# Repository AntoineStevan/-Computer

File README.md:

# The mother board of the µ-C1 project.
This repo and project contain all the files used to create the mother board for the µ-C1 computer project.

## Table Of Content.
 - [0  ](https://github.com/AntoineStevan/uComputer-mother-board/tree/main/#0-prerequisites-toc)  Prerequisites.
 - [1  ](https://github.com/AntoineStevan/uComputer-mother-board/tree/main/#1-some-images-toc)    Some images.
 - [2  ](https://github.com/AntoineStevan/uComputer-mother-board/tree/main/#2-open-in-kicad-toc)  Open in KiCAD.
 - [2.1](https://github.com/AntoineStevan/uComputer-mother-board/tree/main/#21-install-kicad-toc) Install KiCAD.
 - [2.2](https://github.com/AntoineStevan/uComputer-mother-board/tree/main/#22-use-kicad-toc)     Use KiCAD.

## 0. Prerequisites. [[toc](https://github.com/AntoineStevan/uComputer-mother-board/tree/main/#table-of-content)]
Some schematics and footprints are custom.  
One can find them [here](https://github.com/AntoineStevan/kicad-libraries).

## 1 Some images. [[toc](https://github.com/AntoineStevan/uComputer-mother-board/tree/main/#table-of-content)]
||
|:--:|
| *preview of the schematics.* |

||
|:--:|
| *preview of the pcb design (front side).* |

||
|:--:|
| *preview of the pcb design (back side).* |

## 2. Open in KiCAD. [[toc](https://github.com/AntoineStevan/uComputer-mother-board/tree/main/#table-of-content)]
This project has been designed under KiCAD, which is, according to their official website, *an open-source software tool for the creation of electronic schematic diagrams and PCB artwork.*  
All usefull official documentation can be found on the website of the Kicad software [here](https://www.kicad.org/).  
Furthermore, parts have been ordered by [Mouser](https://www.mouser.fr/) and PCBs have been manufactured by [JLCPCB](https://jlcpcb.com/).

### 2.1. Install KiCAD. [[toc](https://github.com/AntoineStevan/uComputer-mother-board/tree/main/#table-of-content)]
Official KiCAD material can be found [here](https://docs.kicad.org/5.1/en/getting_started_in_kicad/getting_started_in_kicad.html).  
Further specific material for Linux users can be found [here](https://doc.ubuntu-fr.org/kicad).

### 2.2. Use KiCAD. [[toc](https://github.com/AntoineStevan/uComputer-mother-board/tree/main/#table-of-content)]
The KiCAD team provides plenty of documentation and examples on their official website [here](https://docs.kicad.org/).  
The Internet is also full of great quality tutorials on many topics concerning KiCAD software and schematics/PCB design in general.

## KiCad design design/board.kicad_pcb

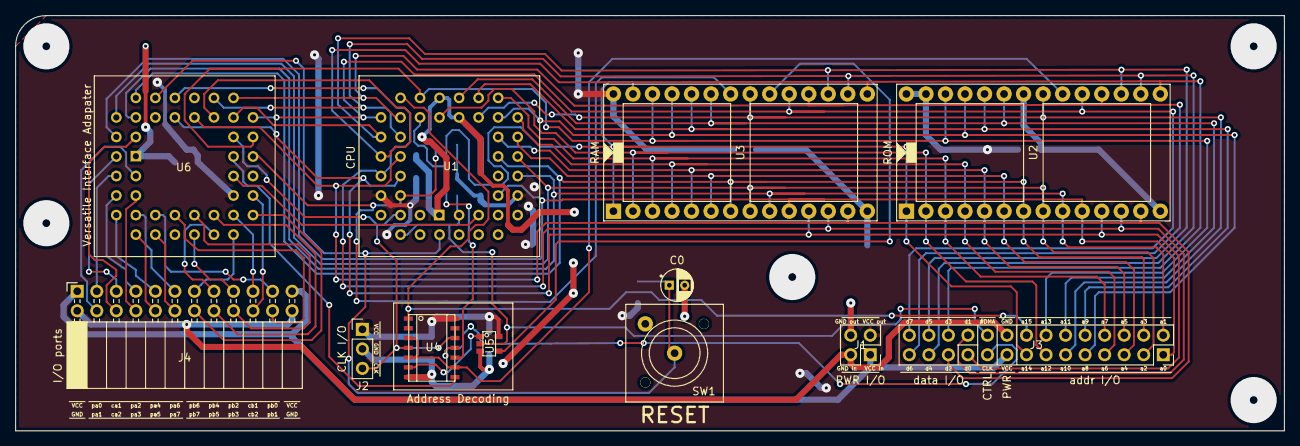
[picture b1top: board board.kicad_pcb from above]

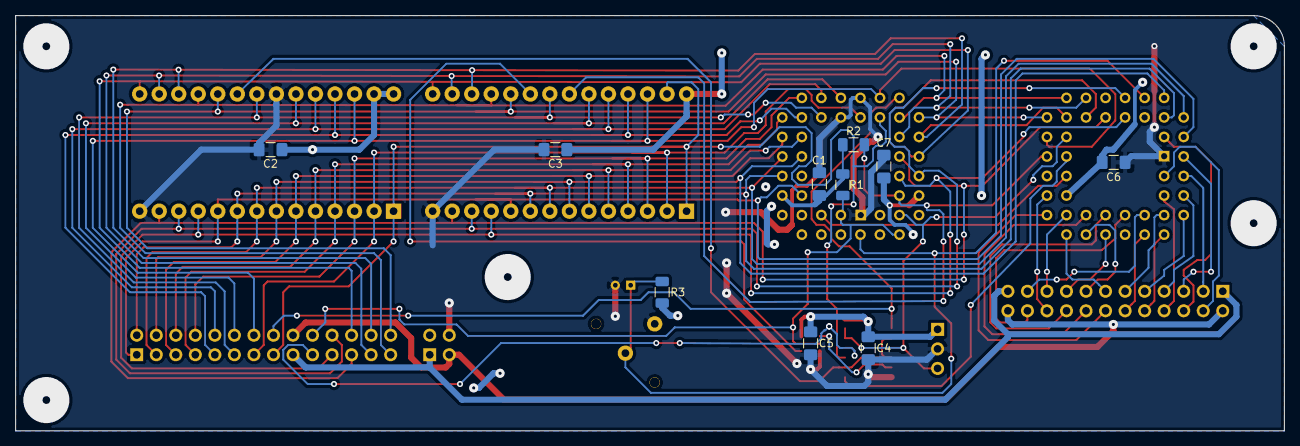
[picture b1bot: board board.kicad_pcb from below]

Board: 2 copper layers, 165.0 x 54.0 mm, 22 parts (10 on the bottom side), 58 nets.

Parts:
C0: C; CP_Radial_D4.0mm_P2.00mm
C1, C2, C3, C4, C5, C6, C7: C; C_1206_3216Metric_Pad1.42x1.75mm_HandSolder
J1: Conn_01x04_Male; PinHeader_2x02_P2.54mm_Vertical
J2: Conn_01x03_Male; PinHeader_1x03_P2.54mm_Vertical
J3: Conn_02x14_Odd_Even; PinSocket_2x14_P2.54mm_Vertical
J4: Conn_02x12_Odd_Even; PinSocket_2x12_P2.54mm_Horizontal
R1, R2, R3: 1K; R_1206_3216Metric
SW1: reset; pushbutton_switch
U1: W65C02_PLCC_44; SOCKET_PLCC_DIP44_A23.5mm_B23.5mm_C12.7mm_D12.7mm_P2.54mm
U2: AT28C256_PDIP_28; DIP_Socket-28_L35.56_W17.78_H5.1_P2.54
U3: SRAM; DIP_Socket-28_L35.56_W17.78_H5.1_P2.54
U4: 74LS00; SOIC_14_L.1.18_W0.58_P1.27
U5: 2-AND; SC-74A_p0.95
U6: W65C22_PLCC_44; SOCKET_PLCC_DIP44_A23.5mm_B23.5mm_C12.7mm_D12.7mm_P2.54mm

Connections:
/#CE: U2.20, U4.3, U4.5, U4.9
/#CLK: J3.19, U4.11
/#CS2: U4.8, U6.25
/#DMA: J3.20, R1.1, U1.3, U1.40, U5.2
/#IRQ: U1.5, U6.23
/#RAM_E: U3.20, U5.4
/#RES: C0.1, R3.1, SW1.2, U1.44, U6.37
/#RW: R2.1, U1.38, U3.22, U6.24
/+5V: C1.1, C2.1, C3.1, C4.1, C5.1, C6.1, C7.1, J1.3, J2.1, R1.2, R2.2, R3.2, U1.9, U1.37, U2.27, U2.28, U3.28, U5.5, U6.21
/CLK: J2.3, U1.41, U4.4, U4.12, U4.13, U6.27
/GND: C0.2, C1.2, C2.2, C3.2, C4.2, C5.2, C6.2, C7.2, J1.4, J2.2, SW1.1, U1.1, U1.23, U1.24, U2.14, U2.22, U3.14, U5.3, U6.1
/MASTER_GND: J1.2, J3.18, J4.2, J4.24
/MASTER_VCC: J1.1, J3.17, J4.1, J4.23
/NAND1: U4.6, U5.1
/a0: J3.1, U1.10, U2.10, U3.10, U6.42
/a1: J3.2, U1.11, U2.9, U3.9, U6.41
/a2: J3.3, U1.13, U2.8, U3.8, U6.40
/a3: J3.4, U1.14, U2.7, U3.7, U6.39
/a4: J3.5, U1.15, U2.6, U3.6
/a5: J3.6, U1.16, U2.5, U3.5
/a6: J3.7, U1.17, U2.4, U3.4
/a7: J3.8, U1.18, U2.3, U3.3
/a8: J3.9, U1.19, U2.25, U3.25
/a9: J3.10, U1.20, U2.24, U3.24
/a10: J3.11, U1.21, U2.21, U3.21
/a11: J3.12, U1.22, U2.23, U3.23
/a12: J3.13, U1.25, U2.2, U3.2
/a13: J3.14, U1.26, U2.26, U3.26, U6.26
/a14: J3.15, U1.27, U2.1, U3.1, U3.27, U4.10
/a15: J3.16, U1.28, U4.1, U4.2
/ca1: J4.5, U6.44
/ca2: J4.6, U6.43
/cb1: J4.19, U6.19
/cb2: J4.20, U6.20
/d0: J3.21, U1.36, U2.11, U3.11, U6.36
/d1: J3.22, U1.35, U2.12, U3.12, U6.35
/d2: J3.23, U1.34, U2.13, U3.13, U6.34
/d3: J3.24, U1.33, U2.15, U3.15, U6.32
/d4: J3.25, U1.32, U2.16, U3.16, U6.31
/d5: J3.26, U1.31, U2.17, U3.17, U6.30
/d6: J3.27, U1.30, U2.18, U3.18, U6.29
/d7: J3.28, U1.29, U2.19, U3.19, U6.28
/pa0: J4.3, U6.2
/pa1: J4.4, U6.3
/pa2: J4.7, U6.4
/pa3: J4.8, U6.5
/pa4: J4.9, U6.6
/pa5: J4.10, U6.7
/pa6: J4.11, U6.8
/pa7: J4.12, U6.9
/pb0: J4.21, U6.10
/pb1: J4.22, U6.12
/pb2: J4.17, U6.13
/pb3: J4.18, U6.14
/pb4: J4.15, U6.15
/pb5: J4.16, U6.16
/pb6: J4.13, U6.17
/pb7: J4.14, U6.18

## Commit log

2021-08-29 Parts list + first schematics of the mother board.
2021-08-30 Replaced old chips with new specific ones + labels.
2021-09-03 New I/O ports.
2021-09-03 README update.
2021-09-03 README correction.
2021-09-04 Interface routing.
2021-09-04 CPU routing.
2021-09-04 Added pcb and net with interface and CPU done.
2021-09-04 Memory routed.
2021-09-04 Corrected AND gate schematics + start on control.
2021-09-05 Adress + data I/O routed.
2021-09-06 All connections done.
2021-09-06 File management.
2021-09-06 gitignore.
2021-09-06 Silk for I/O ports.
2021-09-06 gitignore update + new button footprint name.
2021-09-07 Images + README update.
2021-09-07 Corrected image file paths.
2021-09-07 Removed svg + pcb views + README update.
2021-09-07 Mounting holes.
2021-09-07 Image update.
2021-09-07 Negative of schematics + README path correction.
2021-09-07 Better reset switch.
2021-09-07 Minor changes.
2021-09-11 Link to kicad-libraries + further explainations.
